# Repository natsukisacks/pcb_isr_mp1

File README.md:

# PCB Independent Study MP1 - Spring 2024
## Using Eclectronics Course's MP1

For the first project of our PCB ISR, we wanted to create a simple circuit that would introduce us to the major tools of PCB design, from creating a schematic and layout in KiCad to fabricating the board. This project is based on miniproject 1 of Eclectronics.

### Design Requirements 
These requirements are taken almost verbatim from the miniproject 1 instructions: 
- Your circuit must flash an LED with a period of 1 s.
- Your circuit must run on a single-ended 3.3-V supply that is derived from the 5V VBUS supply in a standard type-A USB port.
- Your circuit design may only use components from the (unmodified) spreadsheet provided with this assignment.
- Your circuit must include adequate bypass and bulk capacitors for the integrated circuits, as specified in their datasheets.
- Your PCB must be a two-layer design with all components on the top side of the board. The minimum allowable trace width and spacing is 6 mils. The minimum allowable via size is 24 mils with a 12-mil drill hole. A small part (i.e., less than 10%) of your grade for this project will be related to the area of your final PCB layout.

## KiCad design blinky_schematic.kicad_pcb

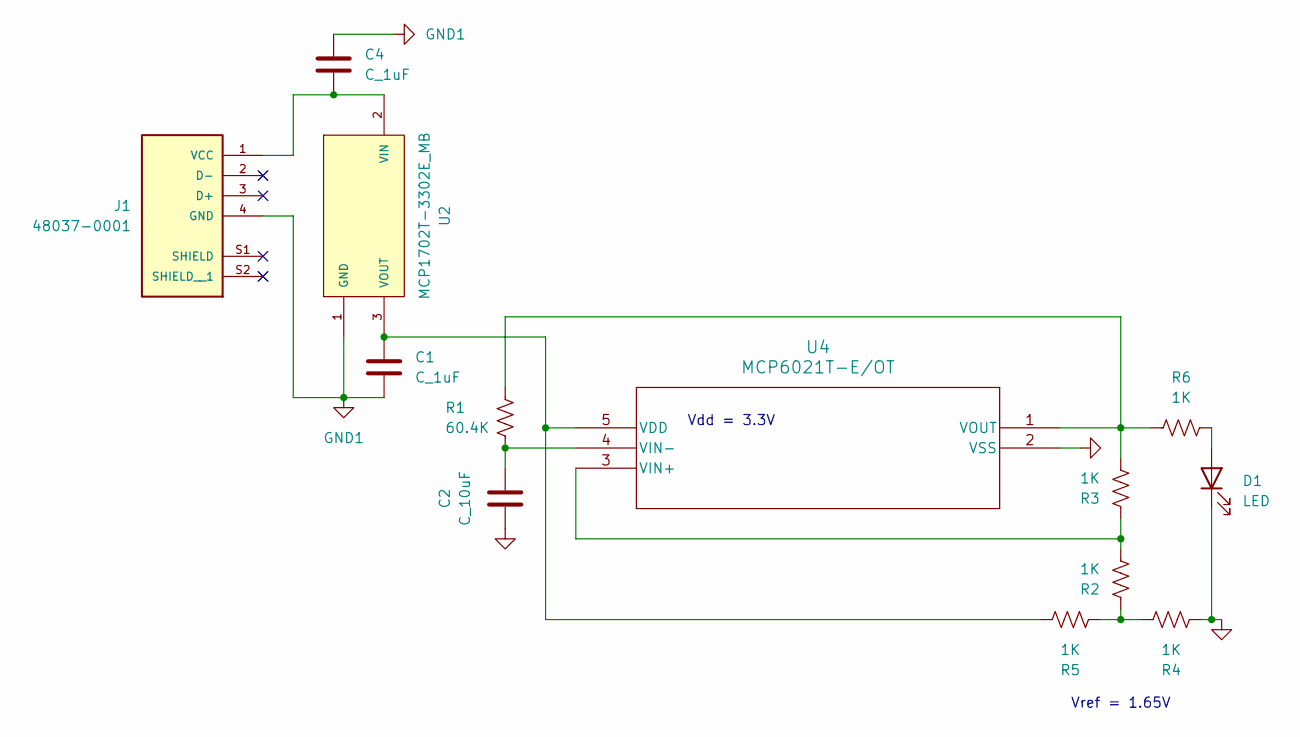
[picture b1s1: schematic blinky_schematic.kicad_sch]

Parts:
C1, C4: C_1uF; C_0603_1608Metric; MPN 1276-6470-1-ND
C2: C_10uF; C_0603_1608Metric; MPN 1276-1052-1-ND
D1: LED; LED_0805_2012Metric
J1: 48037-0001; MOLEX_USB_conn; PARTREV D
R1: 60.4K; R_0603_1608Metric
R2, R3, R4, R5, R6: 1K; R_0603_1608Metric
U2: MCP1702T-3302E_MB; MCP1702T; PARTREV E
U4: MCP6021T-E/OT; MCP6021T

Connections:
GND1: C1.2, C2.1, C4.2, D1.1 (K), J1.4 (GND), R4.1, U2.1 (GND), U4.2 (VSS)
unnamed: D1.2 (A), R6.2
unnamed: C4.1, J1.1 (VCC), U2.2 (VIN)
unnamed: R2.1, R4.2, R5.2
unnamed: C1.1, R5.1, U2.3 (VOUT), U4.5 (VDD)
unnamed: R2.2, R3.1, U4.3 (VIN+)
unnamed: C2.2, R1.2, U4.4 (VIN-)
unnamed: R1.1, R3.2, R6.1, U4.1 (VOUT)

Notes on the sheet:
Vdd = 3.3V
Vref = 1.65V

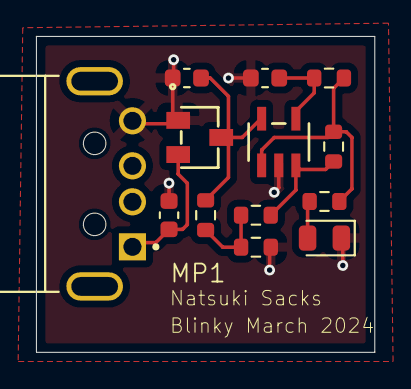
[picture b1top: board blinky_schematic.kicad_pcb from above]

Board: 2 copper layers, 18.8 x 17.5 mm, 13 parts (0 on the bottom side), 8 nets.

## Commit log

2024-05-11 Add blinky kicad files
